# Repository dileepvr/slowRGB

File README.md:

This design is being released under GPL_v3.
All future versions of GPL automatically apply.

This is a kicad project for a circuit for an RGB LED array nightlight
running code on an atmega328p microcontroller.

avr code for microcontroller using arduino libraries will be included.

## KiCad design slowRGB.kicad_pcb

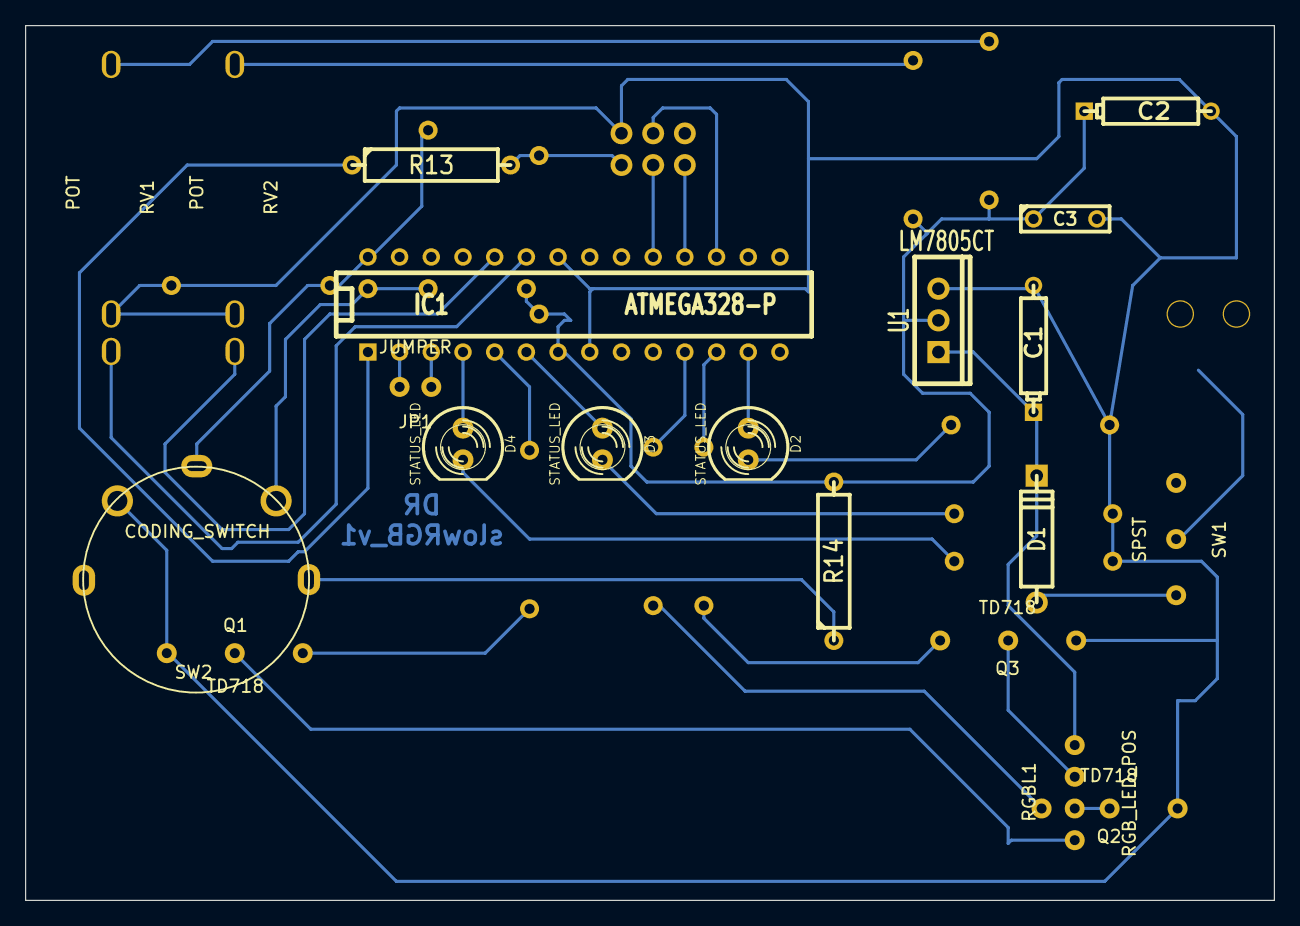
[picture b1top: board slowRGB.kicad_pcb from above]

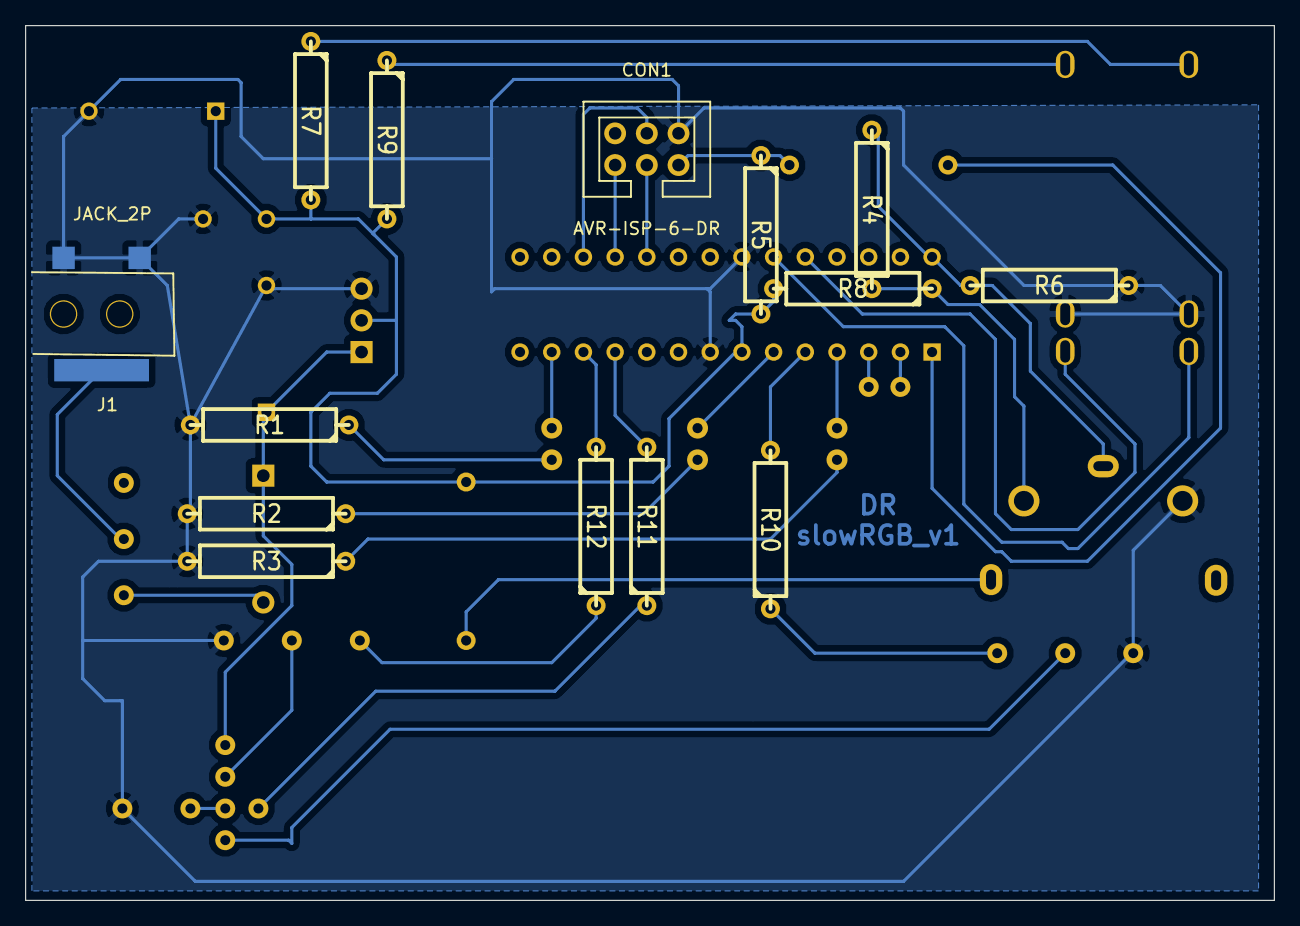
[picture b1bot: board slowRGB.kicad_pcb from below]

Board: 2 copper layers, 100.1 x 70.1 mm, 34 parts (14 on the bottom side), 34 nets.

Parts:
C1: 100U; CP4
C2: 10U; CP4
C3: 1U; C2
CON1: AVR-ISP-6-DR
D1: DIODE; D4
D2, D3, D4: STATUS_LED; LED-5MM
IC1: ATMEGA328-P; DIP-28__300
J1: JACK_2P; Jack_2mm
JP1: JUMPER; jumper_2
Q1, Q2, Q3: TD718
R1, R2, R3, R7, R9: 1K; R5
R4: 5K; R5
R5, R6: 10K; R5
R8: 15K; R5
R10, R11, R12: 200; R5
R13, R14: 0; R5
RGBL1: RGB_LED_POS; RGB_24W
RV1, RV2: POT
SW1: SPST; 6A_switch
SW2: CODING_SWITCH; Coding_switch
U1: LM7805CT; TO220_VERT

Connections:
/5V: C2.1, C3.1, IC1.7, R5.2, R7.2, R8.2, R9.2, R14.2, U1.3
/GND: C1.2, C2.2, C3.2, CON1.6, IC1.8, IC1.22, J1.1, J1.2, Q1.1, Q2.1, Q3.1, R1.2, R2.2, R3.2, R6.1, RV1.1, RV2.1, SW2.2, U1.2
/miso: CON1.1, IC1.18
/mosi: CON1.4, IC1.17
/rst: CON1.5, R5.1, R13.2
/sclk: CON1.3, IC1.19
unnamed: IC1.2, JP1.1
unnamed: IC1.3, JP1.2
unnamed: D4.1, IC1.4
unnamed: IC1.12, R12.2
unnamed: Q1.2, R10.1
unnamed: Q2.2, R11.1
unnamed: IC1.11, R11.2
unnamed: Q3.2, R12.1
unnamed: IC1.1, R13.1
unnamed: R14.1, SW2.5
unnamed: IC1.5, R10.2
unnamed: D2.1, IC1.13
unnamed: D3.1, IC1.6
unnamed: R4.2, R8.1, SW2.4
unnamed: D3.2, R2.1
unnamed: D4.2, R3.1
unnamed: D2.2, R1.1
unnamed: IC1.28, R4.1, R6.2, SW2.3
unnamed: R7.1, RV1.3
unnamed: R9.1, RV2.3
unnamed: Q3.3, RGBL1.2
unnamed: J1.3, SW1.1
unnamed: D1.1, SW1.2
unnamed: C1.1, D1.2, RGBL1.1, U1.1
unnamed: Q2.3, RGBL1.3
unnamed: Q1.3, RGBL1.4
unnamed: IC1.24, RV2.2
unnamed: IC1.23, RV1.2

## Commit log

2016-07-30 kicad files added.
2016-07-30 Added gitignore
